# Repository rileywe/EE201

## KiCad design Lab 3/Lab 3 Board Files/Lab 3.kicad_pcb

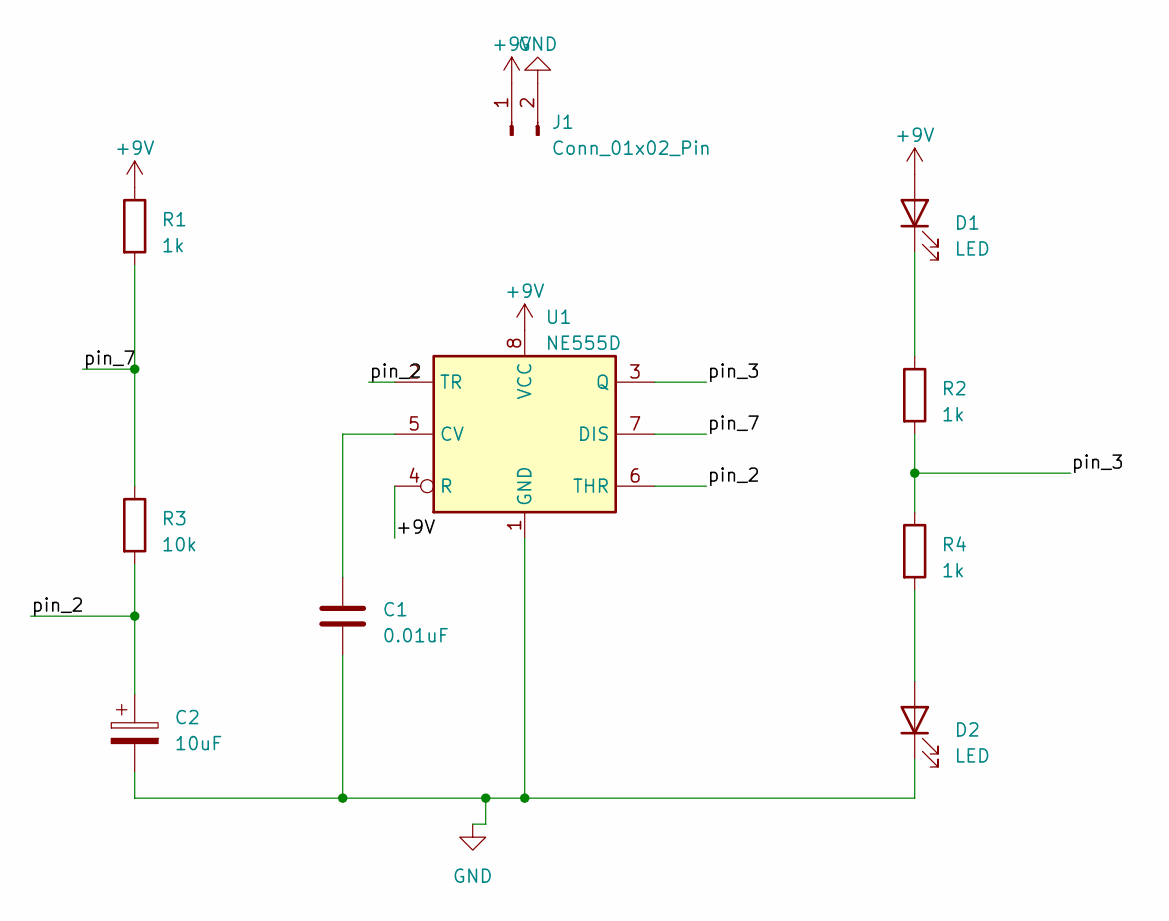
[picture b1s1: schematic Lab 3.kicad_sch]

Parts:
C1: 0.01uF; C_0805_2012Metric_Pad1.18x1.45mm_HandSolder
C2: 10uF; CP_EIA-3216-18_Kemet-A_Pad1.58x1.35mm_HandSolder
D1, D2: LED; LED_1206_3216Metric_Pad1.42x1.75mm_HandSolder
J1: Conn_01x02_Pin; JST_EH_S2B-EH_1x02_P2.50mm_Horizontal
R1, R2, R4: 1k; R_0805_2012Metric_Pad1.20x1.40mm_HandSolder
R3: 10k; R_0805_2012Metric_Pad1.20x1.40mm_HandSolder
U1: NE555D; SOIC-8-1EP_3.9x4.9mm_P1.27mm_EP2.29x3mm

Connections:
+9V: D1.2 (A), J1.1, R1.1, U1.4 (R), U1.8 (VCC)
/pin_2: C2.1, R3.2, U1.2 (TR), U1.6 (THR)
/pin_3: R2.2, R4.1, U1.3 (Q)
/pin_7: R1.2, R3.1, U1.7 (DIS)
GND: C1.2, C2.2, D2.1 (K), J1.2, U1.1 (GND)
unnamed: D1.1 (K), R2.1
unnamed: D2.2 (A), R4.2
unnamed: C1.1, U1.5 (CV)

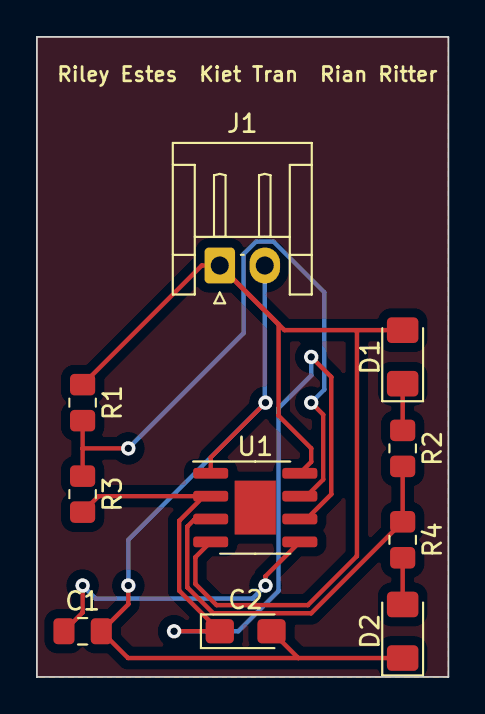
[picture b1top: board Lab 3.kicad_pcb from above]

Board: 2 copper layers, 22.9 x 35.6 mm, 10 parts (0 on the bottom side), 8 nets.

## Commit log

2023-03-30 Lab 1
2023-04-05 Lab 2 Upload
2023-04-13 Lab 3 group commit
2023-04-13 zip file for Lab 3 board files
2023-04-13 uploading lab 3
2023-04-20 Lab 4 submission CAD files
2023-04-20 Lab 4 file management
2023-04-24 added soldermask files
2023-04-27 Lab 5 initial commit
2023-05-04 Lab 6 soldering initial commit
2023-05-31 Final project picture submissions
